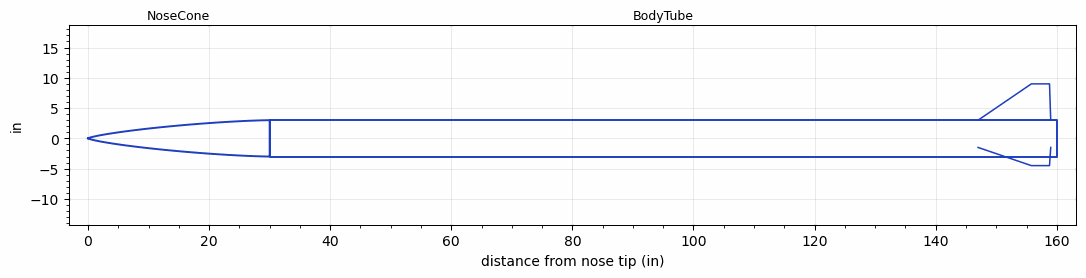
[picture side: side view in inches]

<RASAeroDocument>
 <FileVersion>2</FileVersion>
 <RocketDesign>
  <NoseCone>
   <Length>30</Length>
   <Diameter>6</Diameter>
   <Shape>Von Karman Ogive</Shape>
   <Location>0</Location>
  </NoseCone>
  <BodyTube>
   <Length>130</Length>
   <Diameter>6</Diameter>
   <Location>30</Location>
   <Fin>
    <Count>3</Count>
    <Chord>12</Chord>
    <Span>6</Span>
    <SweepDistance>8.8</SweepDistance>
    <TipChord>3</TipChord>
    <Thickness>0.5</Thickness>
    <Location>13</Location>
    <AirfoilSection>Hexagonal</AirfoilSection>
    <FX1>0.3</FX1>
    <FX3>0.3</FX3>
   </Fin>
  </BodyTube>
  <Surface>Smooth (Zero Roughness)</Surface>
  <ModifiedBarrowman>False</ModifiedBarrowman>
  <Turbulence>False</Turbulence>
  <SustainerNozzle>2.23</SustainerNozzle>
  <UseBooster1>False</UseBooster1>
  <UseBooster2>False</UseBooster2>
 </RocketDesign>
 <LaunchSite>
  <Altitude>1300</Altitude>
  <Pressure>29.97</Pressure>
  <RodAngle>0</RodAngle>
  <RodLength>32</RodLength>
  <Temperature>74</Temperature>
  <WindSpeed>16</WindSpeed>
 </LaunchSite>
 <Recovery>
  <Altitude1>1000</Altitude1>
  <Altitude2>1000</Altitude2>
  <DeviceType1>None</DeviceType1>
  <DeviceType2>None</DeviceType2>
  <Event1>False</Event1>
  <Event2>False</Event2>
  <Size1>1</Size1>
  <Size2>1</Size2>
  <EventType1>None</EventType1>
  <EventType2>None</EventType2>
  <CD1>1.33</CD1>
  <CD2>1.33</CD2>
 </Recovery>
 <SimulationList>
  <Simulation>
   <SustainerEngine>N27-30k(THRUSTMIKEY)  (TAMUSRT-30k)</SustainerEngine>
   <SustainerLaunchWt>155</SustainerLaunchWt>
   <SustainerNozzleDiameter>1.2</SustainerNozzleDiameter>
   <SustainerCG>100.66</SustainerCG>
   <SustainerIgnitionDelay>0</SustainerIgnitionDelay>
   <Booster1SeparationDelay>0</Booster1SeparationDelay>
   <Booster1IgnitionDelay>0</Booster1IgnitionDelay>
   <IncludeBooster1>False</IncludeBooster1>
   <Booster2Delay>0</Booster2Delay>
   <IncludeBooster2>False</IncludeBooster2>
   <TimetoApogee>48.46787</TimetoApogee>
   <MaxAltitude>33192.71</MaxAltitude>
   <MaxVelocity>1465.688</MaxVelocity>
  </Simulation>
 </SimulationList>
</RASAeroDocument>
